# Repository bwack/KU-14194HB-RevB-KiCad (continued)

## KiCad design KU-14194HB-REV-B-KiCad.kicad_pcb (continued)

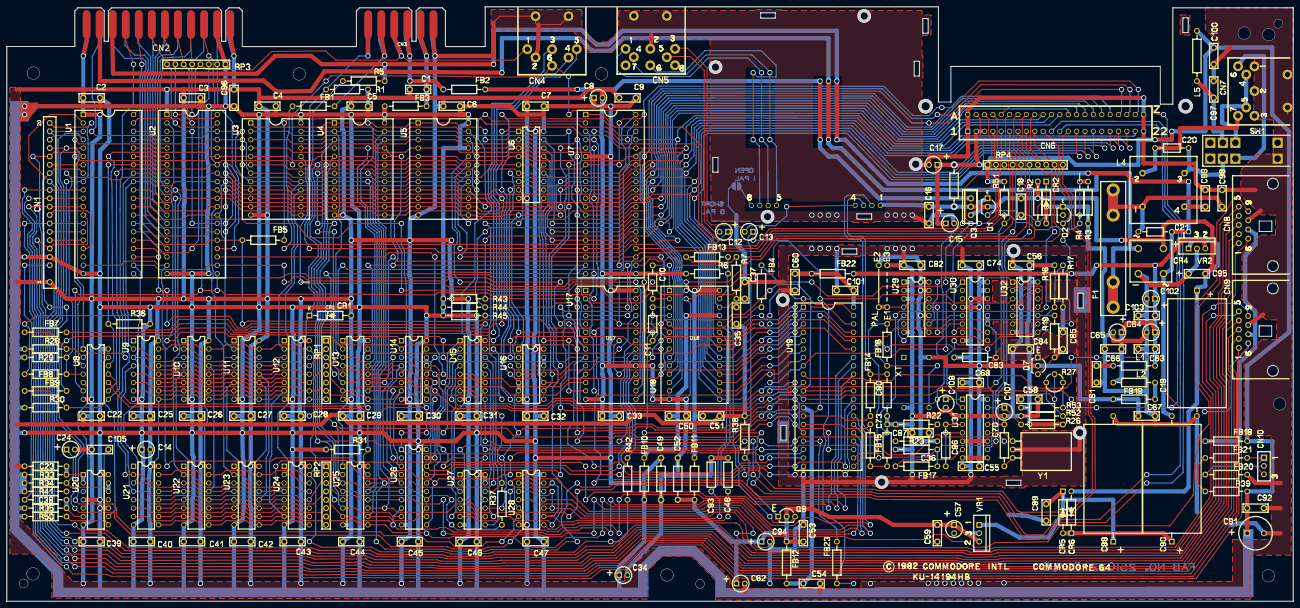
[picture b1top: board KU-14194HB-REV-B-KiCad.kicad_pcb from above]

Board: 2 copper layers, 390.2 x 180.3 mm, 221 parts (0 on the bottom side), 227 nets.

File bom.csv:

Qty,Reference(s),Value,Description,Mouser P/N,Reichelt P/N,Other
56,C1 C2 C3 C4 C5 C6 C7 C9 C16 C18 C22 C25 C26 C27 C28 C29 C30 C31 C32 C33 C39 C40 C41 C42 C43 C44 C45 C46 C47 C49 C50 C51 C52 C53 C54 C56 C58 C59 C60 C61 C63 C66 C67 C68 C74 C84 C89 C92 C95 C96 C98 C99 C101 C103 C105 and one piggybacked over CR1,0.1,Cap MLCC 0.1uF 50V X7R P5.08mm Radial,80-C322C104K5R5TA,X7R-5 100N,
16,C8 C12 C13 C14 C15 C17 C24 C34 C57 C62 C64 C65 C94 C102 C107, C108,10uF,Cap Alu 10uF 25V 5x5mm P2.5mm Radial,667-ECE-A1EKS100I,M 10U 25
2,C10 C11,470pF,Cap MLCC 470pF X7R Axial,594-A471K15X7RF5UAA,?,
1,C19,2200uF,Cap Elyt 2200uF 16V 15x30mm Axial,594-2222-021-16222,COS 105 2200/16,
2,C20 C21,0.22,Cap Polyester Film 0.22uF 63VAC P10mm,594-2222-368-25224,MKS4-100 220N2,
1,C23,350pF,Cap MLCC 350pF 50V C0G Axial,594-A331J15C0GF5TAA,?,
4,C35 C37 C55 C87,NC,-,-,-,
1,C36,20pF,Cap MLCC 20pF C0G Axial,581-SA102A200JAR,?,
1,C38,51pF,Cap MLCC 51pF (47pF OK) X7R Axial,581-SA102A470JAR,?,
2,C48 C93,1800pF,Cap MLCC 1800pF X7R Axial,581-SA101C182KAR,?,
1,C70,15pF 5%,Cap MLCC 15pF 50V 5% C0G Axial/Radial Leaded,594-A150J15C0GH5TAA,KERKO 15P,
2,C83 C86,82pF,Cap MLCC 82pF 100V C0G Axial / Radial Disc,80-C410C820J1G,,
1,C85,0.47,Cap MLCC 0.47uF +80/-20% X7R P5.08mm Radial,80-C330C474K5R,Z5U-5 470N,
2,C88 C90,470uF,Cap Elyt 470uF 50V 20% 13x26mm Axial,598-477TTA050M,COS 105 470/50,
1,C91,100uF,Cap Elyt 100uF 16V 20% 6.3x11mm Radial,80-C330C224K1R,FR-A 100U 16,
2,C97 C100,0.22,Cap MLCC 0.22uF 50V X7R P5.08mm Radial,80-C330C224K1R,Z5U-5 220N,
1,CN1,KEYBOARD_20PIN_MALE,Pin Header 20 POS P2.54mm male vertical,538-22-28-4204,MPE 087-1-020,
1,CN4,SERIAL_BUS_CON,,,,
1,CN5,AV_CONN,,,,
1,CN6,EXPANSION_PORT,Conn Edge Dual Female 44 POS P2.54mm,,,Digikey: H122591-ND
1,CN7,POWER_CON,,,,
2,CN8 CN9,CONTROL_PORT,,571-5747467-1,,
1,CN10,LED_CONNECTOR,Pin Header 3 POS P2.54mm male vertical,538-22-28-4033,RND 205-00624,
1,CR1,IN4371,Zener Diode 2.7V 500mW DO-35-2,78-TZX2V7A,"ZF 2,7",
1,CR2,IN755,Zener Diode 7.5V 500mW DO-35-2,78-TZX7V5C,"ZF 7,5",
1,CR4,BRIDGE_RECTIFIER,Bridge Rectifier 2A 600V Vf=1.05V,627-S2VB60-5000,KBPC604 DIO,
2,CR5 CR6,1N4001,Rectifier 1A Vr=50V,625-1N4001-E3/54,1N 4001,
1,E1,JUMPER_WIRE,,-,-,-
2,F1,1A,Fuse Clips (buy two),504-BK/1A1907-03-R,LITT 01020071Z,
1,FUSE,1A,Fuse Glass 6x32mm 1A 250VAC slow,530-3AG1-R,RND 170-00104,
22,FB4 FB10 FB11 FB12 FB13 FB14 FB15 FB18 FB22 FB1 FB2 FB3 FB5 FB7 FB8 FB9 FB16 FB17 FB19 FB20 FB2 FB23,FERRITE_BEAD,Ferrite Bead 3.6x5mm Axial,81-BL01RN1A2A2B,BEAD 8-21,
2,L1 L2,2.2uH,Inductor 2.2uH 5% Radial,652-78F2R2J-RC,"L-MICC 2,2µ",
1,L4,CHOKE,Common Mode Choke 250V 3.8mH 2.1A 150mOhms,80-SSR10V-21038,,
1,L5,1.2uH,Inductor 1.5uH 10% Radial,542-5800-4R7-RC,"L-HBCC 1,5µ",
1,M1,MODULATOR_LONGBOARD,,,,
4,Q1 Q2 Q7 Q8,2SC1815,Bipolar Transistor TO-92 Vce=60V 400mA,2SC1815,SC 1815,
1,Q3,TP298/2SD880,Bipolar Transistor TO-220,512-KSD880YTU,SD 880,
4,R1 R43 R44 R45,3K3,Resistor 3K3 0207 Axial,594-MBB02070C3301FC1,"METALL 3,30K",
2,R2 R51,1.5K,Resistor 1K5 0207 Axial,594-MBB02070C1501FCT,"1W 1,5K",
2,R3 R7,10K,Resistor 10K 0207 Axial,594-MBB02070C1002FCT,"METALL 10,0K",
10,R4 R6 R16 R28 R29 R30 R31 R36 R38 and one bodge resistor (see images folder),1K,Resistor 1K 0207 Axial,594-MBB02070C1001FCT,"METALL 1,00K",
1,R5,560,Resistor 560 0207 Axial,594-MBB02070C5600FCT,METALL 560,
2,R17 R37,2K7,Resistor 2K7 0207 Axial,594-MBB02070C2701FCT,"METALL 2,70K",
1,R19,15K,Resistor 15K 0207 Axial,594-MBB02070C1502FC1,"METALL 15,0K",
1,R22,0R,Piece of resistor leg,-,-,
1,R23,NC,-,-,-,
2,R26 R53,100,Resistor 100 0207 Axial,594-MBB02070C1000FCT,METALL 100,
1,R27,500,Trimmer Resistor 500 Ohms Linear,652-3306F-1-501,BOU 3386P-1-501,
2,R33 R34,47K,Resistor 47K 0207 Axial,594-MBB02070C4702FC1,"METALL 47,0K",
1,R35,470K,Resistor 470K 0207 Axial,594-MBB02070C4703FCT,METALL 470K,
1,R39,390,Resistor 390 0207 Axial,594-MBB02070C3900FCT,METALL 390,
2,R41 R50,1M,Resistor 1M 0207 Axial,594-MBB02070C1004FCT,,
1,R42,~,-,-,-,
1,R52,330,Resistor 330 0207 Axial,594-MBB02070C3300FCT ,,
2,RP1 RP2,33,Resistor Network 33R Isolated 8 pin SIP,268-33-RC,,
1,RP3,R_ARRAY_7WAY_US,Resistor Network 3K3 Bussed 8 pin SIP,774-77081332P,,
1,RP4,R_ARRAY_9WAY_US,Resistor Network 3K3 Bussed 10 pin SIP,774-770101332P,,
1,SW1,POWER_SWITCH,,,,
1,U1,CIA_U1,,,,
1,U2,CIA_U2,,,,
2,U3 U4,2364A,,,,
1,U5,2332A,,,,
1,U6,2114,,,,
1,U7,6510_MPU,,,,
1,U8,7406N,Logic IC – Hex inverter,595-SN74LS06N,,
8,U9 U10 U11 U12 U21 U22 U23 U24,4164-2,DRAM 1x64kb,,,
1,U13 U25,74LS257,,595-SN74LS257BN,,
1,U14,74LS258,,595-SN74LS258BN ,,
1,U15,74LS139,,595-SN74LS139AN,,
2,U16 U28,4066_U28,,595-CD4066BE,,
1,U17,PLA_U17,,,,
1,U18,6581,,,,
1,U19,VIC,,,,
1,U20,556,,595-NE556NE4,,
1,U26,74LS373,,595-SN74LS373N,,
1,U27,7408_U27,,595-SN74LS08N,,
1,U29,74LS74,,595-SN74LS74AN,,
1,U30,74LS193,,595-SN74LS193N,,
1,U31,74LS629N,,595-SN74LS629N ,,
1,U32,MC4044,,,,
1,VR1,7812,,926-LM2940CT-12/NOPB,,
1,VR2,7805,,511-L4941BV,,
1,XT1,NOT USED,,,,
1,Y1,Crystal,Crystals 17.73447MHz 30ppm HC-49 18pF,815-AB-17.734475-B4,"17,7344-HC49U-S",
C23,360 → 350,,,,,

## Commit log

2019-08-27 schematics update
2019-09-02 more connectors and stuff
2019-09-03 added missing parts. powre connector is upside down in the ku board
2019-09-06 oscillator
2019-09-08 Oscillator area
2019-09-19 More schematics
2019-09-26 Tighter ram symbols. Getting closer to the end of the schematics.
2019-09-28 Almost done now
2019-09-28 PDF update
2019-09-28 Schematics PDF and screenshot update
2019-09-28 screenshot of 3d rendering
2019-09-29 AV connector, Not used parts, pdf update
2019-09-30 Polygons to fill zones. Reducing DRC errors.
2019-10-05 Replica 1.0
2019-10-15 V1.1 Layout: Fixed missing keying-slot in user port.
2019-11-10 Rev 1.2
    Added missing C14
2019-11-12 Update V1.3
    See readme
2019-11-12 V1.3 C70
2019-11-18 value updates
2020-01-01 Added instructions to necessary fixes to Commodores mistakes
2020-01-04 adding a bom for replica 1.3
2020-01-22 Rev 1.4. See Readme
2020-09-12 removed solder paste from edge connectors. moved the solder mask openings from the board to the edge connectors themselves.
2020-09-12 Added outline drawings (Dwgs.User layer) on the edge connectors for those who want to reuse these footprints in another design, the can use these lines as guide for the edge.cut layer (kicad does not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
2020-12-29 interactive-bom generated using plugin
2020-12-29 typo in the readme
2021-01-10 moved silkscreen from board to footprint library
2021-03-10 moved silkscreen into some commodore-part footprints
2021-03-14 Moving silscreen art from board to footprints
2021-04-01 Update README.md with the Interactive-BOM preview.
2021-04-10 Updated README.md. Added link to forum64.de thread "Bilder Showroom"
2021-07-26 added *rescue.lib to the repo, including some small changes to the bom #5
2021-07-26 added the rescue lib for real this time #5
2021-11-22 Added Disclaimer Link
